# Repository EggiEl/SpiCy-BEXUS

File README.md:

# SpiCy-BEXUS
Please take a look at the [wiki](https://github.com/EggiEl/SpiCy-BEXUS/wiki) for documentation of electrical and software.

### About
This is the official GitHub repository of the SpiCy-BEXUS team, dedicated to code sharing and documentation for our project.

<table align="center">
  <tr>
    <td align="center">
      
    </td>
    <td align="center">
      
    </td>
    <td align="center">
      
    </td>
  </tr>
  <tr>
    <td align="center">
      
    </td>
    <td align="center">
      
    </td>
    <td align="center">
      
    </td>
  </tr>
  <tr>
    <td align="center">
      
    </td>
    <td align="center">
      
    </td>
    <td align="center">
      
    </td>
  </tr>
</table>

### Project Overview
SpiCy (Stratospheric investigation of combinatory cyanobacterial biofilms) is a student-led mission to investigate the behavior of combinatory cyanobacterial biofilms under increased ionizing and non-ionizing radiation levels in the stratosphere to propose new alternatives of oxygen suppliance during space travel missions.

Cyanobacteria are among the oldest and most efficient photosynthetic organisms on planet Earth. They contribute 25% of the oxygen on Earth today and were crucial in forming our atmosphere in the early stages of Earth's development through oxygenation. As they are mostly aquatic or at least, need a certain degree of humidity, heterotrophic bacteria as a biofilm coordinator to mitigate their dependency are incorporated. These biofilms are a promising candidate in a plethora of space-related research (i.e. medicinal, life). Through forming adhesive biofilms, the bacteria are more resilient to radiation, thermal shocks, mechanical tearing and dry environments. 

Project SpiCy intends to capitalize on the cyanobacterial ability to produce oxygen with minimum requirements and research their viability in long-term oxygen generation for human space flight and colonization missions.

This github documents the technical side of things.

### Contact Us
Take a look at our [Website](https://spicybexus.de/)

### Setup
#### Node 
https://nodejs.org/en/download

#### MongoDB Community Server: 
https://www.mongodb.com/try/download/community

#### How to setup Project after cloning: 

In the root of the Project use:
```
pip install -r requirements.txt
npm install
```

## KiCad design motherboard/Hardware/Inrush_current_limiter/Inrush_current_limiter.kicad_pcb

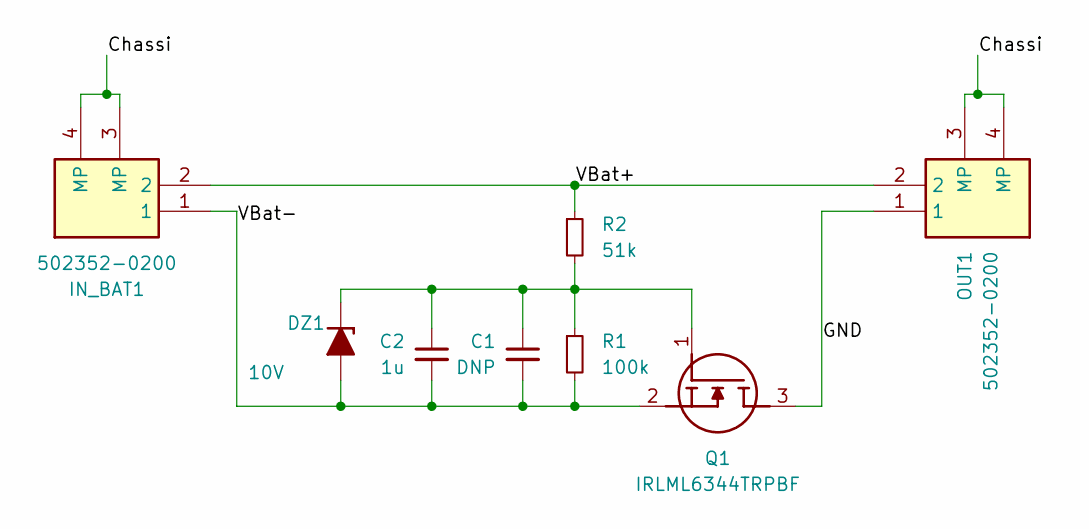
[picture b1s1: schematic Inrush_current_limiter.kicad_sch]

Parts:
C1: DNP; C_0603_1608Metric_Pad1.08x0.95mm_HandSolder
C2: 1u; C_0603_1608Metric_Pad1.08x0.95mm_HandSolder
DZ1: 10V; D_A-405_P2.54mm_Vertical_KathodeUp
IN_BAT1: 502352-0200; 5023520200; Mouser Part Number 538-502352-0200
OUT1: 502352-0200; 5023520200; Mouser Part Number 538-502352-0200
Q1: IRLML6344TRPBF; SOT95P237X112-3N; Mouser Part Number 942-IRLML6344TRPBF
R1: 100k; R_0603_1608Metric_Pad0.98x0.95mm_HandSolder
R2: 51k; R_0603_1608Metric_Pad0.98x0.95mm_HandSolder

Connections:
/Chassi: IN_BAT1.3 (MP), IN_BAT1.4 (MP), OUT1.3 (MP), OUT1.4 (MP)
/GND: OUT1.1, Q1.3 (D)
/VBat+: IN_BAT1.2, OUT1.2, R2.1
/VBat-: C1.2, C2.2, DZ1.2 (A), IN_BAT1.1, Q1.2 (S), R1.2
unnamed: C1.1, C2.1, DZ1.1 (K), Q1.1 (G), R1.1, R2.2

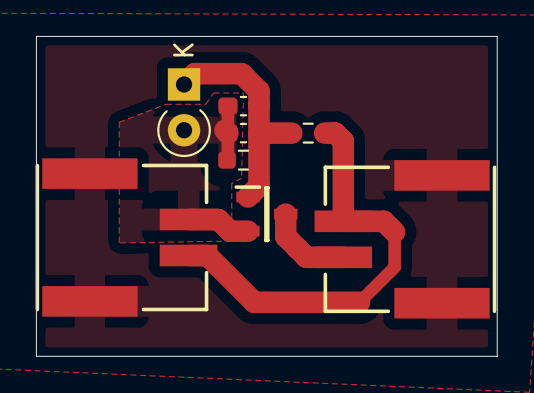
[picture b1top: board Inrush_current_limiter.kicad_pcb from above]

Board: 2 copper layers, 25.6 x 17.8 mm, 8 parts (0 on the bottom side), 5 nets.

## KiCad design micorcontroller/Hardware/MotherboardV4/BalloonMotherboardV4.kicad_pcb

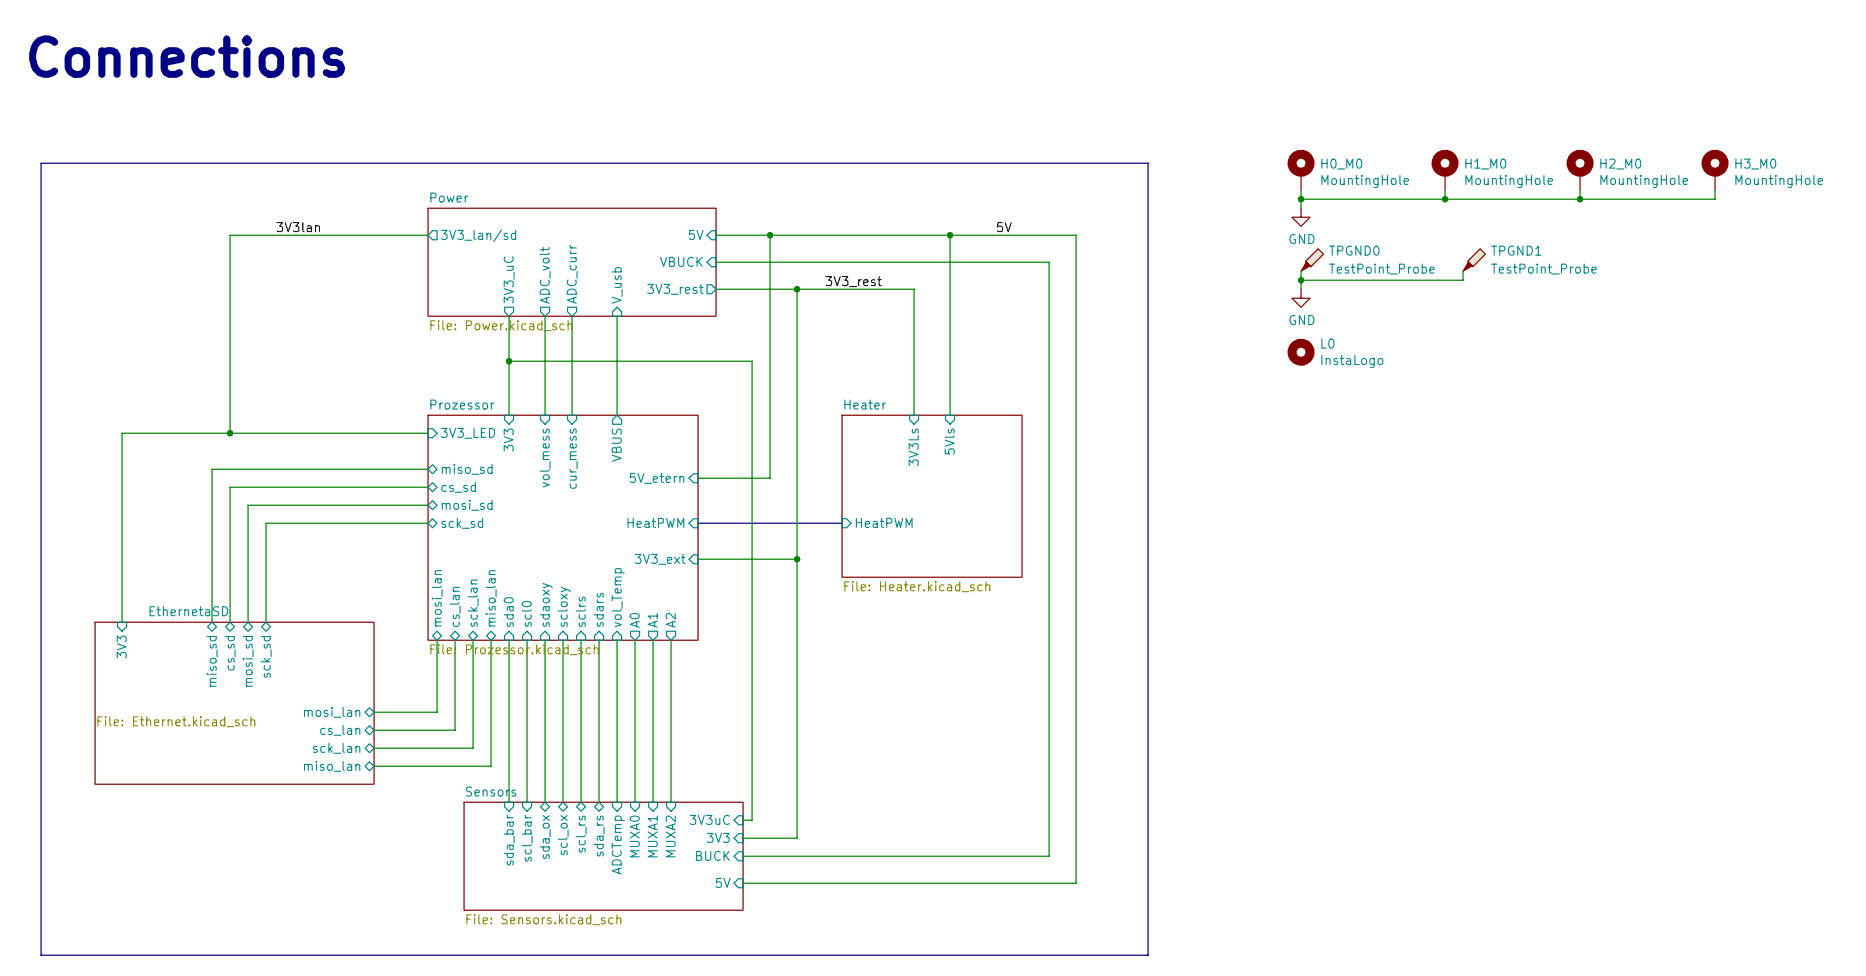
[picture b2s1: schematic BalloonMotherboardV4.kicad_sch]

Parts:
H0_M0, H1_M0, H2_M0, H3_M0: MountingHole; MountingHole_2.2mm_M2_Pad_Via
L0: InstaLogo; insta
TPGND0, TPGND1: TestPoint_Probe; TestPoint_Loop_D1.80mm_Drill1.0mm_Beaded

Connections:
GND: H0_M0.1, H1_M0.1, H2_M0.1, H3_M0.1, TPGND0.1, TPGND1.1; also elsewhere on the board

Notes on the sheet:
Connections

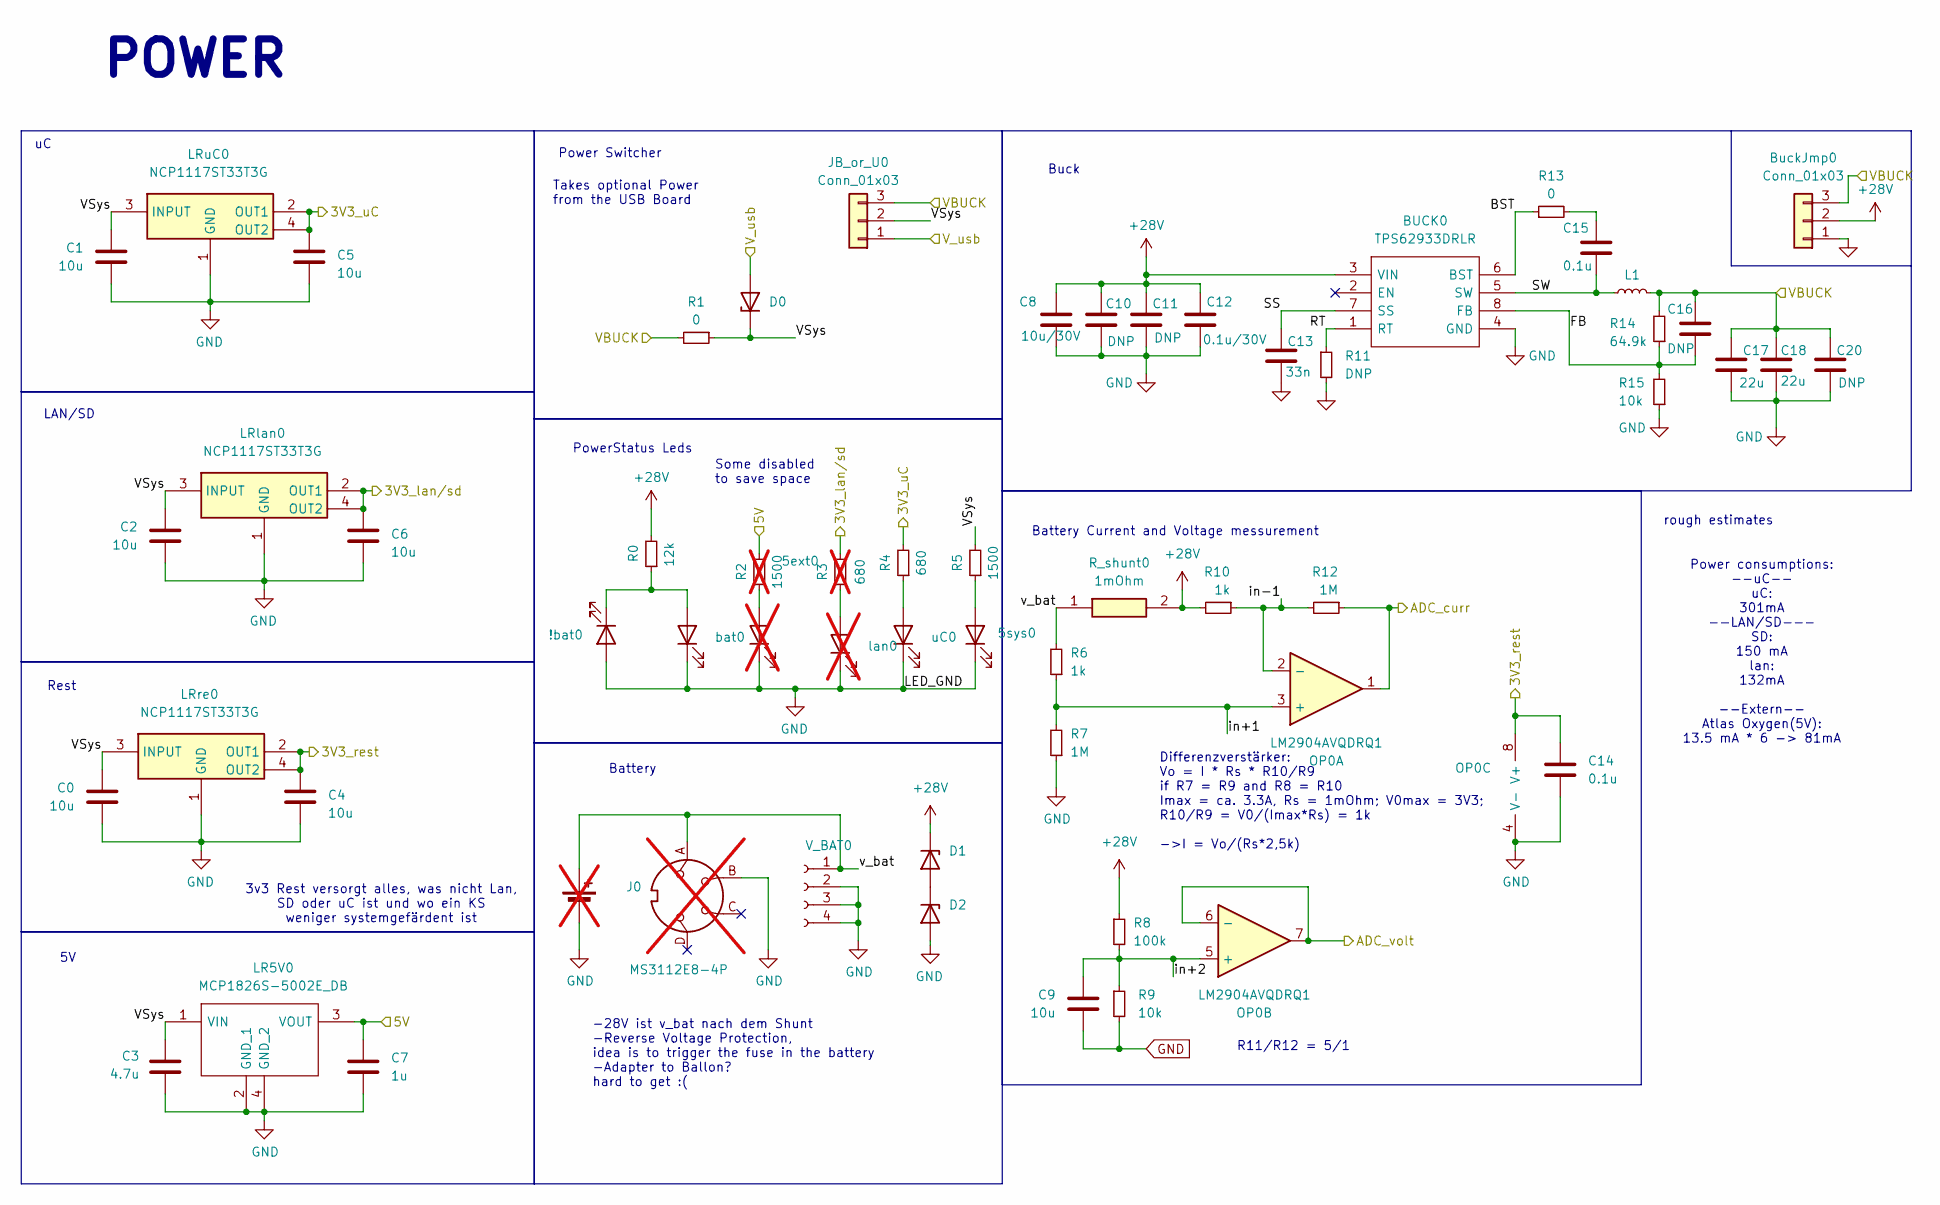
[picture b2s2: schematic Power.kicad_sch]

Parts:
5ext0: APTD2012LCGCK; LEDC2012X120N; Mouser Part Number 604-APTD2012LCGCK; not fitted
5sys0: APTD2012LCGCK; LEDC2012X120N; Mouser Part Number 604-APTD2012LCGCK
!bat0: APTD2012LSURCK; LEDM2012X120N; Mouser Part Number 604-APTD2012LSURCK
BT0: Battery_Cell; not fitted
BUCK0: TPS62933DRLR; SOTFL50P160X60-8N; Mouser Part Number 595-TPS62933DRLR
BuckJmp0: Conn_01x03; PinHeader_1x03_P2.54mm_Vertical
C0, C1, C2, C4, C5, C6, C9: 10u; C_0805_2012Metric_Pad1.18x1.45mm_HandSolder
C3: 4.7u; C_0805_2012Metric_Pad1.18x1.45mm_HandSolder
C7: 1u; C_0402_1005Metric_Pad0.74x0.62mm_HandSolder
C8: 10u/30V; C_0805_2012Metric_Pad1.18x1.45mm_HandSolder
C10, C11, C20: DNP; C_0805_2012Metric_Pad1.18x1.45mm_HandSolder
C12: 0.1u/30V; C_0402_1005Metric_Pad0.74x0.62mm_HandSolder
C13: 33n; C_0805_2012Metric_Pad1.18x1.45mm_HandSolder
C14, C15: 0.1u; C_0402_1005Metric_Pad0.74x0.62mm_HandSolder
C16: DNP; C_0402_1005Metric_Pad0.74x0.62mm_HandSolder
C17, C18: 22u; C_0805_2012Metric_Pad1.18x1.45mm_HandSolder
D0, D1, D2: RBR2LB60BTBR1; DIOM5336X245N; Mouser Part Number 755-RBR2LB60BTBR1
J0: MS3112E8-4P; Mouser Part Number 654-MS3112E8-4P; not fitted
JB_or_U0: Conn_01x03; PinHeader_1x03_P2.54mm_Vertical
L1: 74439346068; Mouser Part Number 710-74439346068
LR5V0: MCP1826S-5002E_DB; SOT230P700X180-4N; Mouser Part Number 579-MCP1826S-5002EDB
LRlan0: NCP1117ST33T3G; SOT230P700X180-4N; Mouser Part Number 863-NCP1117ST33T3G
LRre0: NCP1117ST33T3G; SOT230P700X180-4N; Mouser Part Number 863-NCP1117ST33T3G
LRuC0: NCP1117ST33T3G; SOT230P700X180-4N; Mouser Part Number 863-NCP1117ST33T3G
OP0: LM2904AVQDRQ1; SOIC127P600X175-8N
R0: 12k; R_0603_1608Metric_Pad0.98x0.95mm_HandSolder
R1, R13: 0; R_0603_1608Metric_Pad0.98x0.95mm_HandSolder
R2: 1500; R_0603_1608Metric_Pad0.98x0.95mm_HandSolder; not fitted
R3: 680; R_0603_1608Metric_Pad0.98x0.95mm_HandSolder; not fitted
R4: 680; R_0603_1608Metric_Pad0.98x0.95mm_HandSolder
R5: 1500; R_0603_1608Metric_Pad0.98x0.95mm_HandSolder
R6, R10: 1k; R_0603_1608Metric_Pad0.98x0.95mm_HandSolder
R7, R12: 1M; R_0603_1608Metric_Pad0.98x0.95mm_HandSolder
R8: 100k; R_0603_1608Metric_Pad0.98x0.95mm_HandSolder
R9, R15: 10k; R_0603_1608Metric_Pad0.98x0.95mm_HandSolder
R11: DNP; R_0603_1608Metric_Pad0.98x0.95mm_HandSolder
R14: 64.9k; R_0603_1608Metric_Pad0.98x0.95mm_HandSolder
R_shunt0: 1mOhm; RESC3216X90N; Mouser Part Number 603-PA1206FRE7W0R01Z
V_BAT0: 502352-0200; 5023520200; Mouser Part Number 538-502352-0200
bat0: APTD2012LCGCK; LEDC2012X120N; Mouser Part Number 604-APTD2012LCGCK
lan0: APTD2012LCGCK; LEDC2012X120N; Mouser Part Number 604-APTD2012LCGCK; not fitted
uC0: APTD2012LCGCK; LEDC2012X120N; Mouser Part Number 604-APTD2012LCGCK

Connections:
+28V: BUCK0.3 (VIN), BuckJmp0.2, C8.2, C10.2, C11.2, C12.2, D1.1 (K), R0.2, R8.1, R10.2, R_shunt0.2; also elsewhere on the board
/3V3_rest: C4.2, C14.2, LRre0.2 (OUT1), LRre0.4 (OUT2), OP0.8 (V+); also elsewhere on the board
/3V3lan: C6.2, LRlan0.2 (OUT1), LRlan0.4 (OUT2), R3.2; also elsewhere on the board
/5V: C7.2, LR5V0.3 (VOUT), R2.2; also elsewhere on the board
/Power/3V3_uC: C5.2, LRuC0.2 (OUT1), LRuC0.4 (OUT2), R4.2; also elsewhere on the board
/Power/ADC_curr: OP0.1, R12.1; also elsewhere on the board
/Power/ADC_volt: OP0.6 (-), OP0.7; also elsewhere on the board
/Power/BST: BUCK0.6 (BST), R13.1
/Power/FB: BUCK0.8 (FB), C16.2, R14.1, R15.2
/Power/RT: BUCK0.1 (RT), R11.1
/Power/SS: BUCK0.7 (SS), C13.2
/Power/SW: BUCK0.5 (SW), C15.1, L1.1
/Power/VBUCK: BuckJmp0.3, C16.1, C17.2, C18.2, C20.2, JB_or_U0.3, L1.2, R1.2, R14.2; also elsewhere on the board
/Power/VSys: C0.2, C1.2, C2.2, C3.1, D0.1 (K), JB_or_U0.2, LR5V0.1 (VIN), LRlan0.3 (INPUT), LRre0.3 (INPUT), LRuC0.3 (INPUT), R1.1, R5.2
/Power/V_usb: D0.2 (A), JB_or_U0.1; also elsewhere on the board
/Power/in+1: OP0.3 (+), R6.1, R7.2
/Power/in+2: C9.2, OP0.5 (+), R8.2, R9.1
/Power/in-1: OP0.2 (-), R10.1, R12.2
/Power/v_bat: BT0.1 (+), J0.A, R6.2, R_shunt0.1, V_BAT0.1
GND: 5ext0.1 (K), 5sys0.1 (K), !bat0.2 (A), BT0.2 (-), BUCK0.4 (GND), BuckJmp0.1, C0.1, C1.1, C2.1, C3.2, C4.1, C5.1, C6.1, C7.1, C8.1, C9.1, C10.1, C11.1, C12.1, C13.1, C14.1, C17.1, C18.1, C20.1, D2.2 (A), J0.B, LR5V0.2 (GND_1), LR5V0.4 (GND_2), LRlan0.1 (GND), LRre0.1 (GND), LRuC0.1 (GND), OP0.4 (V-), R7.1, R9.2, R11.2, R15.1, V_BAT0.2, V_BAT0.3, V_BAT0.4, bat0.1 (K), lan0.1 (K), uC0.1 (K); also elsewhere on the board
unnamed: 5ext0.2 (A), R2.1
unnamed: 5sys0.2 (A), R5.1
unnamed: !bat0.1 (K), R0.1, bat0.2 (A)
unnamed: C15.2, R13.2
unnamed: D1.2 (A), D2.1 (K)
unnamed: R3.1, lan0.2 (A)
unnamed: R4.1, uC0.2 (A)

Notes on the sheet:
Power consumptions: --uC-- uC: 301mA --LAN/SD--- SD: 150 mA lan: 132mA --Extern-- Atlas Oxygen(5V): 13.5 mA * 6 -> 81mA
Rest
Differenzverstärker: Vo = I * Rs * R10/R9 if R7 = R9 and R8 = R10 Imax = ca. 3.3A, Rs = 1mOhm; V0max = 3V3; R10/R9 = V0/(Imax*Rs) = 1k ->I = Vo/(Rs*2,5k)
PowerStatus Leds
Power Switcher
LAN/SD
POWER
Battery
-28V ist v_bat nach dem Shunt -Reverse Voltage Protection, idea is to trigger the fuse in the battery -Adapter to Ballon? hard to get :(
rough estimates
Takes optional Power from the USB Board
Buck
Battery Current and Voltage messurement
3v3 Rest versorgt alles, was nicht Lan, SD oder uC ist und wo ein KS weniger systemgefärdent ist
R11/R12 = 5/1
Some disabled to save space

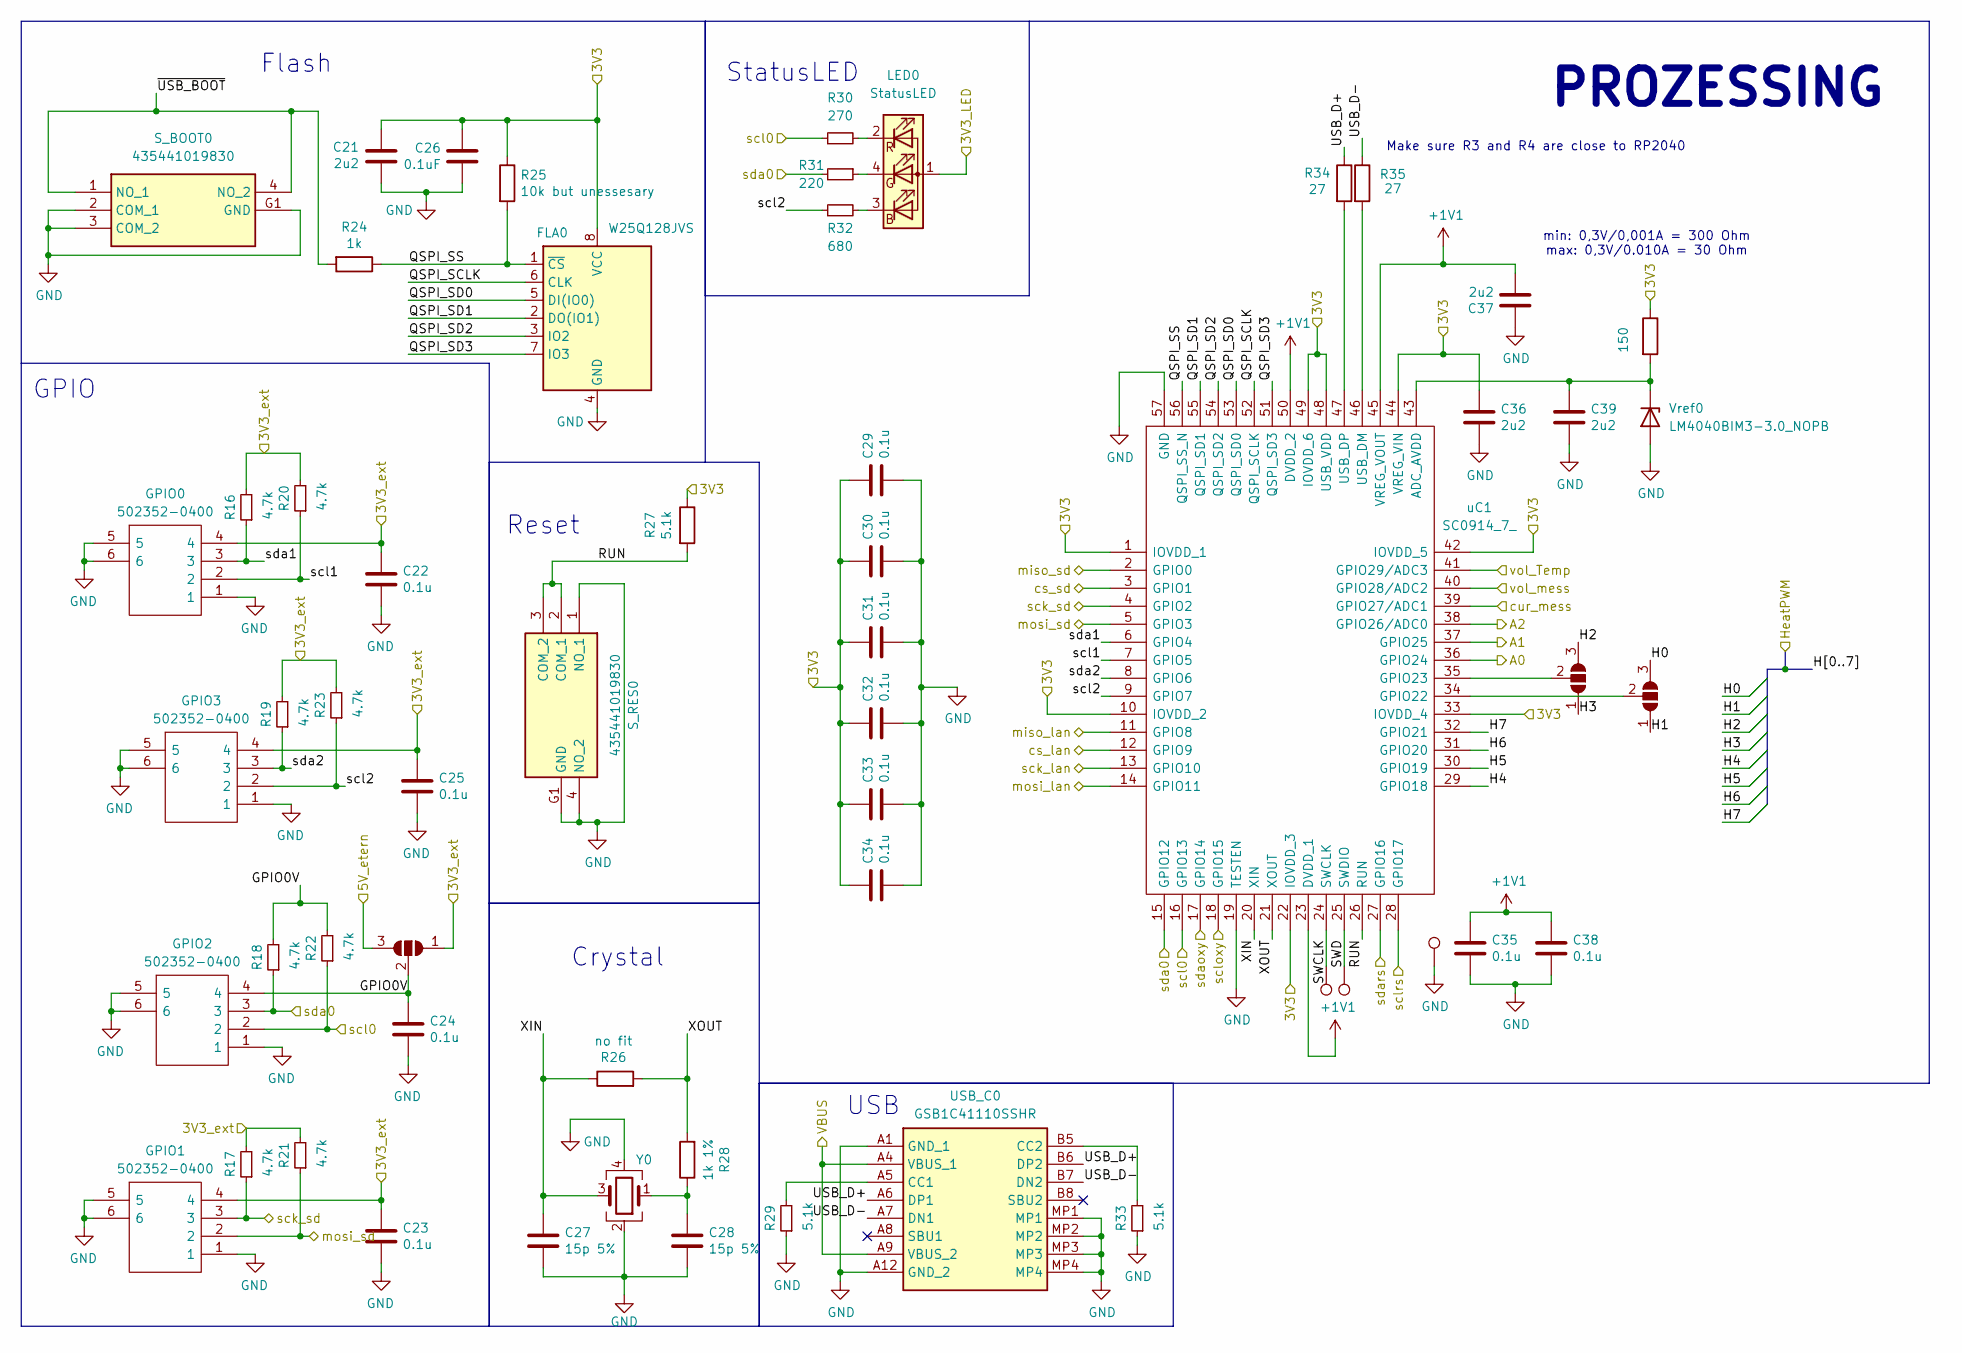
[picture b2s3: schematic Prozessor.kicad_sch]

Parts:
C21, C36, C37, C39: 2u2; C_0805_2012Metric_Pad1.18x1.45mm_HandSolder
C22, C23, C24, C25, C29, C30, C31, C32, C33, C34, C35, C38: 0.1u; C_0402_1005Metric_Pad0.74x0.62mm_HandSolder
C26: 0.1uF; C_0402_1005Metric_Pad0.74x0.62mm_HandSolder
C27, C28: 15p 5%; C_0402_1005Metric_Pad0.74x0.62mm_HandSolder
FLA0: W25Q128JVS; SOIC-8_5.23x5.23mm_P1.27mm
GPIO0, GPIO1, GPIO2, GPIO3: 502352-0400; 5023520400; Mouser Part Number 538-502352-0400
JP0, JP1, JP2: SolderJumper_3_Open; SolderJumper-3_P1.3mm_Open_RoundedPad1.0x1.5mm_NumberLabels
LED0: StatusLED; LTRBR37G4R4S01250; Mouser Part Number 720-LTRBR37GA6714
R16, R17, R18, R19, R20, R21, R22, R23: 4.7k; R_0603_1608Metric_Pad0.98x0.95mm_HandSolder
R24: 1k; R_0603_1608Metric_Pad0.98x0.95mm_HandSolder
R25: 10k but unessesary; R_0603_1608Metric_Pad0.98x0.95mm_HandSolder
R26: no fit; R_0402_1005Metric_Pad0.72x0.64mm_HandSolder
R27, R29, R33: 5.1k; R_0603_1608Metric_Pad0.98x0.95mm_HandSolder
R28: 1k 1%; R_0603_1608Metric_Pad0.98x0.95mm_HandSolder
R30: 270; R_0603_1608Metric_Pad0.98x0.95mm_HandSolder
R31: 220; R_0603_1608Metric_Pad0.98x0.95mm_HandSolder
R32: 680; R_0603_1608Metric_Pad0.98x0.95mm_HandSolder
R34, R35: 27; R_0603_1608Metric_Pad0.98x0.95mm_HandSolder
R36: 150; R_0603_1608Metric_Pad0.98x0.95mm_HandSolder
S_BOOT0: 435441019830; Mouser Part Number 710-435441019830
S_RES0: 435441019830; Mouser Part Number 710-435441019830
TP0, TP1, TP2: TestPoint; TestPoint_Pad_D1.0mm
USB_C0: GSB1C41110SSHR; Manufacturer_Part_Number GSB1C41110SSHR
Vref0: LM4040BIM3-3.0_NOPB; SOT95P237X112-3N; Mouser Part Number 926-LM4040BIM330NOPB
Y0: ABM8G-12.000MHZ-4Y-T3; ABM8G; Mouser Part Number 815-ABM8G-12-4YT3
uC1: SC0914_7_; QFN40P700X700X90-57N-D; Mouser Part Number 358-SC09147

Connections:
+1V1: C35.1, C37.2, C38.1, uC1.23 (DVDD_1), uC1.45 (VREG_VOUT), uC1.50 (DVDD_2)
/3V3_rest: C22.1, C23.1, C25.1, GPIO0.4, GPIO1.4, GPIO3.4, JP0.1 (A), R16.2, R17.2, R19.2, R20.2, R21.2, R23.2; also elsewhere on the board
/3V3lan: LED0.1 (A); also elsewhere on the board
/5V: JP0.3 (B); also elsewhere on the board
/EthernetaSD/cs_lan: uC1.12 (GPIO9); also elsewhere on the board
/EthernetaSD/cs_sd: uC1.3 (GPIO1); also elsewhere on the board
/EthernetaSD/miso_lan: uC1.11 (GPIO8); also elsewhere on the board
/EthernetaSD/miso_sd: uC1.2 (GPIO0); also elsewhere on the board
/EthernetaSD/mosi_lan: uC1.14 (GPIO11); also elsewhere on the board
/EthernetaSD/mosi_sd: GPIO1.2, R21.1, uC1.5 (GPIO3); also elsewhere on the board
/EthernetaSD/sck_lan: uC1.13 (GPIO10); also elsewhere on the board
/EthernetaSD/sck_sd: GPIO1.3, R17.1, uC1.4 (GPIO2); also elsewhere on the board
/Heater/H0: JP2.3 (B); also elsewhere on the board
/Heater/H1: JP2.1 (A); also elsewhere on the board
/Heater/H2: JP1.3 (B); also elsewhere on the board
/Heater/H3: JP1.1 (A); also elsewhere on the board
/Heater/H4: uC1.29 (GPIO18); also elsewhere on the board
/Heater/H5: uC1.30 (GPIO19); also elsewhere on the board
/Heater/H6: uC1.31 (GPIO20); also elsewhere on the board
/Heater/H7: uC1.32 (GPIO21); also elsewhere on the board
/Power/3V3_uC: C21.2, C26.1, C29.1, C30.1, C31.1, C32.1, C33.1, C34.1, C36.1, FLA0.8 (VCC), R25.1, R27.1, R36.1, uC1.1 (IOVDD_1), uC1.10 (IOVDD_2), uC1.22 (IOVDD_3), uC1.33 (IOVDD_4), uC1.42 (IOVDD_5), uC1.44 (VREG_VIN), uC1.48 (USB_VDD), uC1.49 (IOVDD_6); also elsewhere on the board
/Power/ADC_curr: uC1.39 (GPIO27/ADC1); also elsewhere on the board
/Power/ADC_volt: uC1.40 (GPIO28/ADC2); also elsewhere on the board
/Power/V_usb: USB_C0.A4 (VBUS_1), USB_C0.A9 (VBUS_2); also elsewhere on the board
/Prozessor/A0: uC1.36 (GPIO24); also elsewhere on the board
/Prozessor/A1: uC1.37 (GPIO25); also elsewhere on the board
/Prozessor/A2: uC1.38 (GPIO26/ADC0); also elsewhere on the board
/Prozessor/GPIO0V: C24.1, GPIO2.4, JP0.2 (C), R18.2, R22.2
/Prozessor/QSPI_SCLK: FLA0.6 (CLK), uC1.52 (QSPI_SCLK)
/Prozessor/QSPI_SD0: FLA0.5 (DI(IO0)), uC1.53 (QSPI_SD0)
/Prozessor/QSPI_SD1: FLA0.2 (DO(IO1)), uC1.55 (QSPI_SD1)
/Prozessor/QSPI_SD2: FLA0.3 (IO2), uC1.54 (QSPI_SD2)
/Prozessor/QSPI_SD3: FLA0.7 (IO3), uC1.51 (QSPI_SD3)
/Prozessor/QSPI_SS: FLA0.1 (~CS), R24.1, R25.2, uC1.56 (QSPI_SS_N)
/Prozessor/RUN: R27.2, S_RES0.2 (COM_1), S_RES0.3 (COM_2), uC1.26 (RUN)
/Prozessor/SWCLK: TP0.1, uC1.24 (SWCLK)
/Prozessor/SWD: TP1.1, uC1.25 (SWDIO)
/Prozessor/USB_D+: R34.1, USB_C0.A6 (DP1), USB_C0.B6 (DP2)
/Prozessor/USB_D-: R35.1, USB_C0.A7 (DN1), USB_C0.B7 (DN2)
/Prozessor/XIN: C27.1, R26.1, Y0.3, uC1.20 (XIN)
/Prozessor/XOUT: R26.2, R28.2, uC1.21 (XOUT)
/Prozessor/scl0: GPIO2.2, R22.1, R30.1, uC1.16 (GPIO13); also elsewhere on the board
/Prozessor/scl1: GPIO0.2, R20.1, uC1.7 (GPIO5)
/Prozessor/scl2: GPIO3.2, R23.1, R32.1, uC1.9 (GPIO7)
/Prozessor/scloxy: uC1.18 (GPIO15); also elsewhere on the board
/Prozessor/sclrs: uC1.28 (GPIO17); also elsewhere on the board
/Prozessor/sda0: GPIO2.3, R18.1, R31.2, uC1.15 (GPIO12); also elsewhere on the board
/Prozessor/sda1: GPIO0.3, R16.1, uC1.6 (GPIO4)
/Prozessor/sda2: GPIO3.3, R19.1, uC1.8 (GPIO6)
/Prozessor/sdaoxy: uC1.17 (GPIO14); also elsewhere on the board
/Prozessor/sdars: uC1.27 (GPIO16); also elsewhere on the board
/Prozessor/vol_Temp: uC1.41 (GPIO29/ADC3); also elsewhere on the board
/Prozessor/~USB_BOOT: R24.2, S_BOOT0.1 (NO_1), S_BOOT0.4 (NO_2)
GND: C21.1, C22.2, C23.2, C24.2, C25.2, C26.2, C27.2, C28.2, C29.2, C30.2, C31.2, C32.2, C33.2, C34.2, C35.2, C36.2, C37.1, C38.2, C39.2, FLA0.4 (GND), GPIO0.1, GPIO0.5, GPIO0.6, GPIO1.1, GPIO1.5, GPIO1.6, GPIO2.1, GPIO2.5, GPIO2.6, GPIO3.1, GPIO3.5, GPIO3.6, R29.1, R33.1, S_BOOT0.2 (COM_1), S_BOOT0.3 (COM_2), S_BOOT0.G1 (GND), S_RES0.1 (NO_1), S_RES0.4 (NO_2), S_RES0.G1 (GND), TP2.1, USB_C0.A1 (GND_1), USB_C0.A12 (GND_2), USB_C0.MP1, USB_C0.MP2, USB_C0.MP3, USB_C0.MP4, Vref0.2 (A), Y0.2, Y0.4, uC1.19 (TESTEN), uC1.57 (GND); also elsewhere on the board
unnamed: C28.1, R28.1, Y0.1
unnamed: JP1.2 (C), uC1.35 (GPIO23)
unnamed: JP2.2 (C), uC1.34 (GPIO22)
unnamed: LED0.3 (BK), R32.2
unnamed: LED0.4 (GK), R31.1
unnamed: LED0.2 (RK), R30.2
unnamed: R29.2, USB_C0.A5 (CC1)
unnamed: R33.2, USB_C0.B5 (CC2)
unnamed: C39.1, R36.2, Vref0.1 (K), uC1.43 (ADC_AVDD)
unnamed: R35.2, uC1.46 (USB_DM)
unnamed: R34.2, uC1.47 (USB_DP)

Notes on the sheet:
Reset
min: 0,3V/0,001A = 300 Ohm max: 0,3V/0.010A = 30 Ohm
StatusLED
Crystal
Flash
USB
Make sure R3 and R4 are close to RP2040
PROZESSING
GPIO

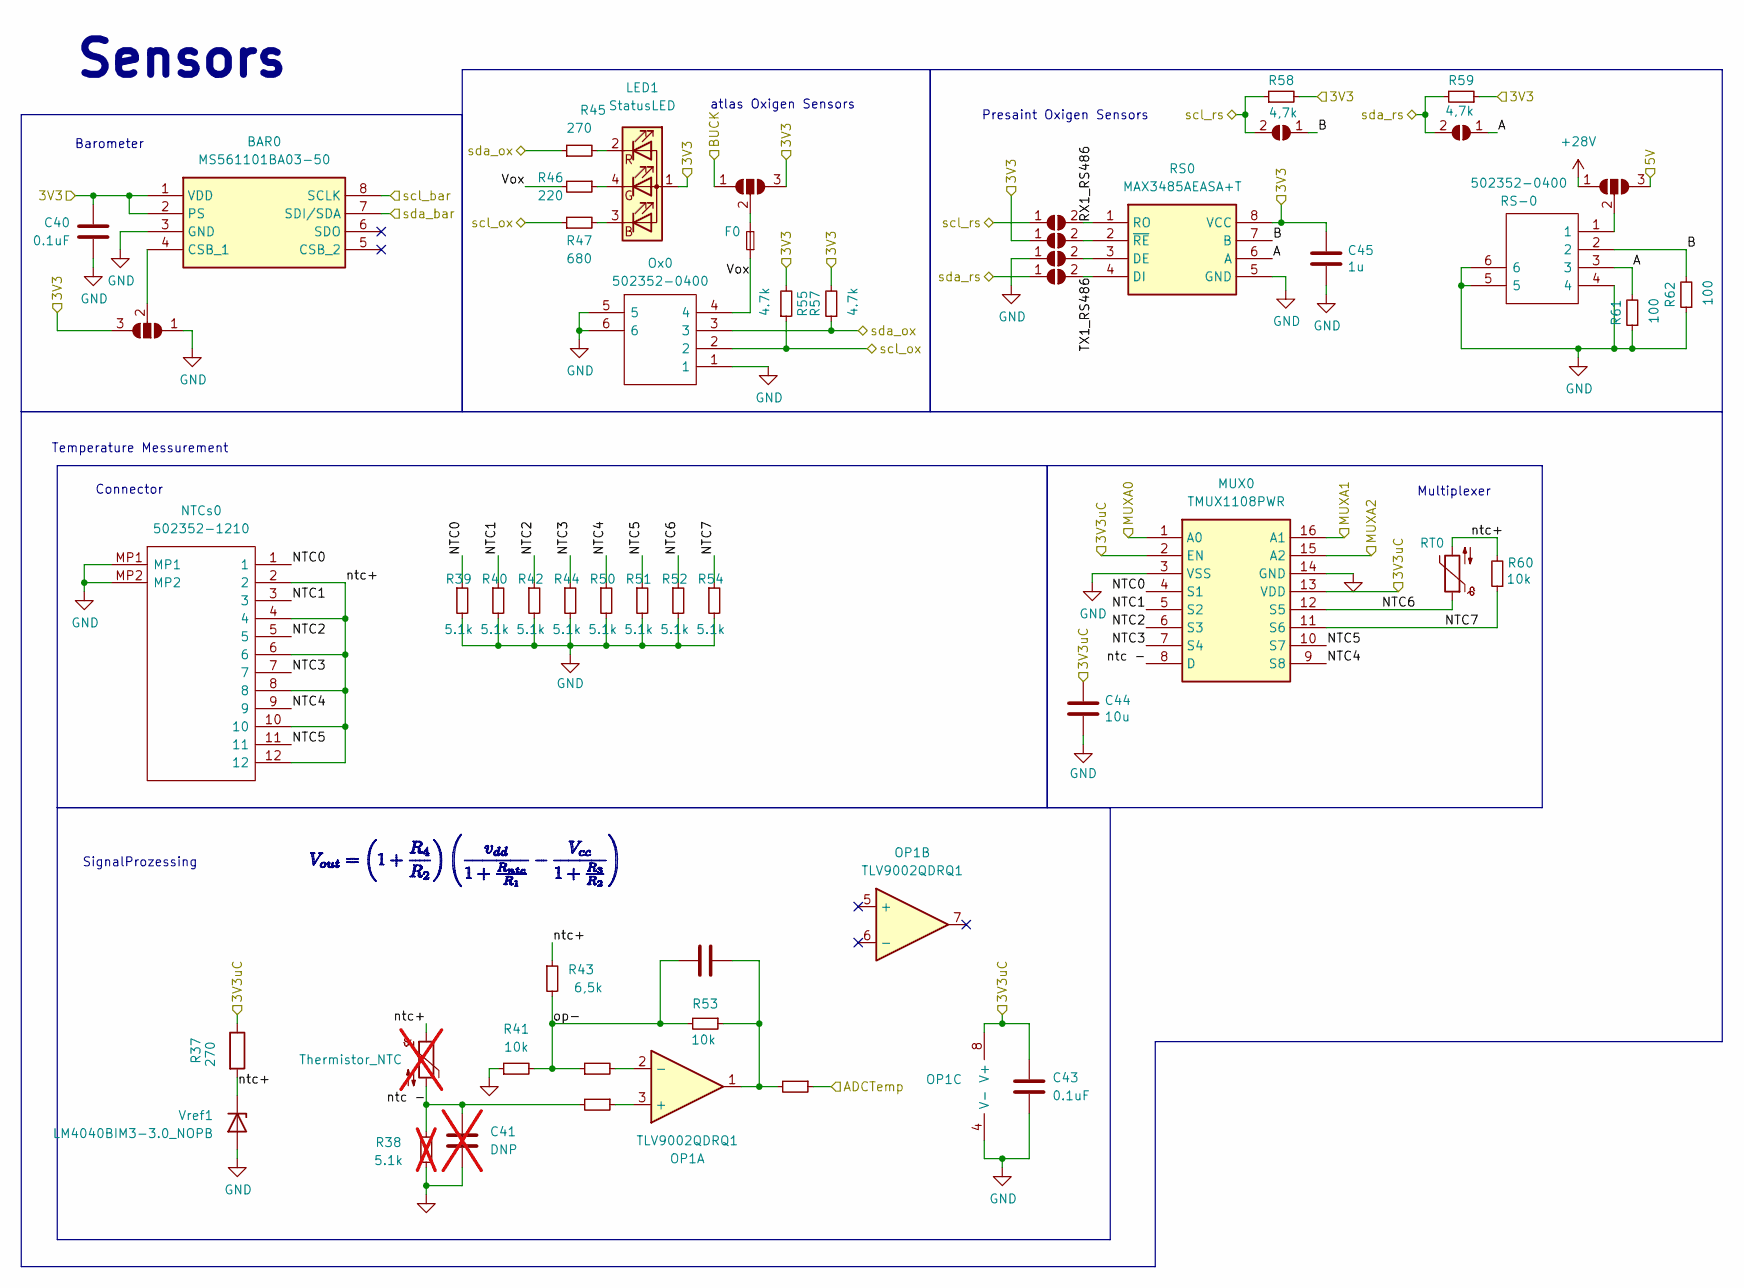
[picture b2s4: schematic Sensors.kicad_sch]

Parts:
BAR0: MS561101BA03-50; Mouser Part Number 824-MS561101BA03-50
C40, C43: 0.1uF; C_0402_1005Metric_Pad0.74x0.62mm_HandSolder
C41: DNP; C_0402_1005Metric_Pad0.74x0.62mm_HandSolder; not fitted
C42: DNP; C_0402_1005Metric_Pad0.74x0.62mm_HandSolder
C44: 10u; C_0805_2012Metric_Pad1.18x1.45mm_HandSolder
C45: 1u; C_0402_1005Metric_Pad0.74x0.62mm_HandSolder
F0: MF-FSML100_8-2; FUSC1608X70N; Mouser Part Number 652-MF-FSML100/8-2
JP3, JP4, JP5, JP6, JP7, JP8: SolderJumper_2_Open; SolderJumper-2_P1.3mm_Open_RoundedPad1.0x1.5mm
JP9: SolderJumper_3_Open; SolderJumper-3_P1.3mm_Open_RoundedPad1.0x1.5mm_NumberLabels
JPVOX0, JPVOX1: SolderJumper_3_Open; SolderJumper-3_P1.3mm_Open_RoundedPad1.0x1.5mm_NumberLabels
LED1: StatusLED; LTRBR37G4R4S01250; Mouser Part Number 720-LTRBR37GA6714
MUX0: TMUX1108PWR; SOP65P640X120-16N; Mouser Part Number 595-TMUX1108PWR
NTCs0: 502352-1210; 5023521210; Mouser Part Number 538-502352-1210
OP1: TLV9002QDRQ1; SOIC127P600X175-8N
Ox0: 502352-0400; 5023520400; Mouser Part Number 538-502352-0400
R37, R45: 270; R_0603_1608Metric_Pad0.98x0.95mm_HandSolder
R38: 5.1k; R_0603_1608Metric_Pad0.98x0.95mm_HandSolder; not fitted
R39, R40, R42, R44, R50, R51, R52, R54: 5.1k; R_0603_1608Metric_Pad0.98x0.95mm_HandSolder
R41, R53, R60: 10k; R_0603_1608Metric_Pad0.98x0.95mm_HandSolder
R43: 6,5k; R_0603_1608Metric_Pad0.98x0.95mm_HandSolder
R46: 220; R_0603_1608Metric_Pad0.98x0.95mm_HandSolder
R47: 680; R_0603_1608Metric_Pad0.98x0.95mm_HandSolder
R48, R49, R56: 1k; R_0603_1608Metric_Pad0.98x0.95mm_HandSolder
R55, R57: 4.7k; R_0603_1608Metric_Pad0.98x0.95mm_HandSolder
R58, R59: 4,7k; R_0603_1608Metric_Pad0.98x0.95mm_HandSolder
R61, R62: 100; R_0603_1608Metric_Pad0.98x0.95mm_HandSolder
RS0: MAX3485AEASA+T; SOIC127P600X175-8N; Mouser Part Number 700-MAX3485AEASA+T
RS-0: 502352-0400; 5023520400; Mouser Part Number 538-502352-0400
RT0: NTCGS163JF103FT8; THRMC1608X90N; Mouser Part Number 810-NTCGS163JF103FT8
TH0: Thermistor_NTC; not fitted
Vref1: LM4040BIM3-3.0_NOPB; SOT95P237X112-3N; Mouser Part Number 926-LM4040BIM330NOPB

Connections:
+28V: JP9.1 (A); also elsewhere on the board
/3V3_rest: BAR0.1 (VDD), BAR0.2 (PS), C40.2, C45.1, JP4.1 (A), JPVOX0.3 (B), JPVOX1.3 (B), LED1.1 (A), R55.2, R57.2, R58.2, R59.1, RS0.8 (VCC); also elsewhere on the board
/5V: JP9.3 (B); also elsewhere on the board
/Power/3V3_uC: C43.2, C44.1, MUX0.2 (EN), MUX0.13 (VDD), OP1.8 (V+), R37.1; also elsewhere on the board
/Power/VBUCK: JPVOX1.1 (A); also elsewhere on the board
/Prozessor/A0: MUX0.1 (A0); also elsewhere on the board
/Prozessor/A1: MUX0.16 (A1); also elsewhere on the board
/Prozessor/A2: MUX0.15 (A2); also elsewhere on the board
/Prozessor/scl0: BAR0.8 (SCLK); also elsewhere on the board
/Prozessor/scloxy: Ox0.2, R47.1, R55.1; also elsewhere on the board
/Prozessor/sclrs: JP3.1 (A), JP7.2 (B), R58.1; also elsewhere on the board
/Prozessor/sda0: BAR0.7 (SDI/SDA); also elsewhere on the board
/Prozessor/sdaoxy: Ox0.3, R45.1, R57.1; also elsewhere on the board
/Prozessor/sdars: JP6.1 (A), JP8.2 (B), R59.2; also elsewhere on the board
/Prozessor/vol_Temp: R56.1; also elsewhere on the board
/Sensors/A: JP8.1 (A), R61.2, RS0.6 (A), RS-0.3
/Sensors/B: JP7.1 (A), R62.2, RS0.7 (B), RS-0.2
/Sensors/NTC0: MUX0.4 (S1), NTCs0.1, R39.1
/Sensors/NTC1: MUX0.5 (S2), NTCs0.3, R40.1
/Sensors/NTC2: MUX0.6 (S3), NTCs0.5, R42.1
/Sensors/NTC3: MUX0.7 (S4), NTCs0.7, R44.1
/Sensors/NTC4: MUX0.9 (S8), NTCs0.9, R50.1
/Sensors/NTC5: MUX0.10 (S7), NTCs0.11, R51.1
/Sensors/NTC6: MUX0.12 (S5), R52.1, RT0.1
/Sensors/NTC7: MUX0.11 (S6), R54.1, R60.1
/Sensors/RX1_RS486: JP3.2 (B), RS0.1 (RO)
/Sensors/TX1_RS486: JP6.2 (B), RS0.4 (DI)
/Sensors/Vox: F0.1, Ox0.4, R46.2
/Sensors/ntc -: C41.2, MUX0.8 (D), R38.1, R49.2, TH0.2
/Sensors/ntc+: NTCs0.2, NTCs0.4, NTCs0.6, NTCs0.8, NTCs0.10, NTCs0.12, R37.2, R43.1, R60.2, RT0.2, TH0.1, Vref1.1 (K)
/Sensors/op-: C42.2, R41.2, R43.2, R48.1, R53.2
GND: BAR0.3 (GND), C40.1, C41.1, C43.1, C44.2, C45.2, JP5.1 (A), JPVOX0.1 (A), MUX0.3 (VSS), MUX0.14 (GND), NTCs0.MP1, NTCs0.MP2, OP1.4 (V-), Ox0.1, Ox0.5, Ox0.6, R38.2, R39.2, R40.2, R41.1, R42.2, R44.2, R50.2, R51.2, R52.2, R54.2, R61.1, R62.1, RS0.5 (GND), RS-0.4, RS-0.5, RS-0.6, Vref1.2 (A); also elsewhere on the board
unnamed: BAR0.4 (CSB_1), JPVOX0.2 (C)
unnamed: C42.1, OP1.1, R53.1, R56.2
unnamed: JP4.2 (B), RS0.2 (~RE)
unnamed: JP5.2 (B), RS0.3 (DE)
unnamed: JP9.2 (C), RS-0.1
unnamed: F0.2, JPVOX1.2 (C)
unnamed: LED1.3 (BK), R47.2
unnamed: LED1.4 (GK), R46.1
unnamed: LED1.2 (RK), R45.2
unnamed: OP1.3 (+), R49.1
unnamed: OP1.2 (-), R48.2

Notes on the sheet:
atlas Oxigen Sensors
Connector
Multiplexer
Temperature Messurement
Sensors
Barometer
SignalProzessing
Presaint Oxigen Sensors
